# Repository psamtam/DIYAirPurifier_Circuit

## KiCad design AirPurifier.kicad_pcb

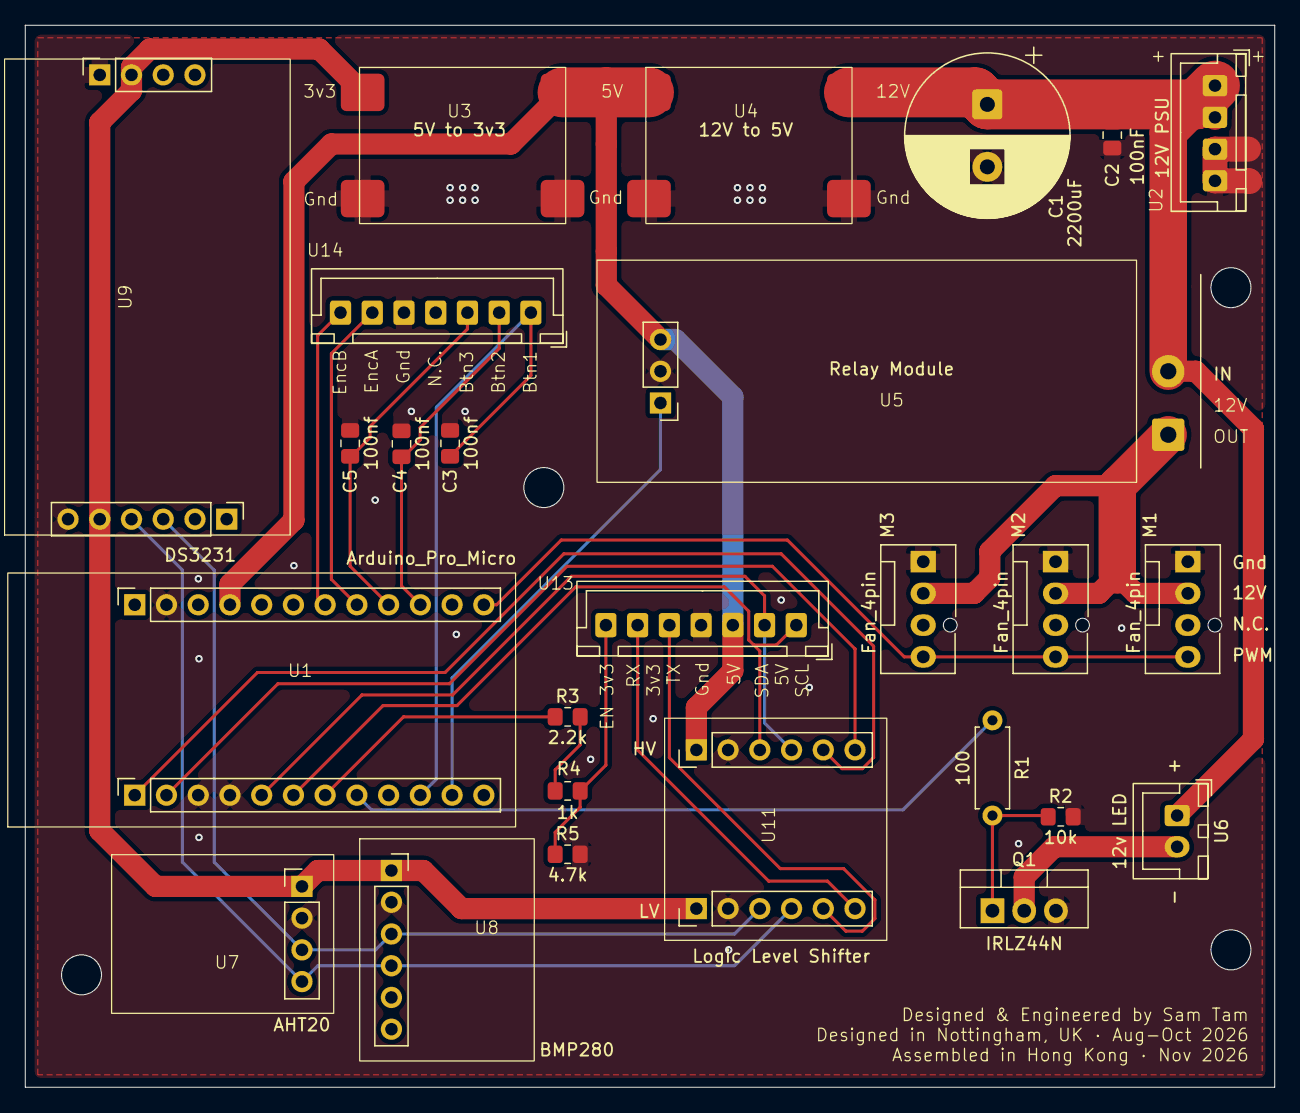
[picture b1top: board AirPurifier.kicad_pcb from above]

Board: 2 copper layers, 100.0 x 85.0 mm, 30 parts (0 on the bottom side), 26 nets.

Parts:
C1: 2200uF; CP_Radial_D13.0mm_P5.00mm
C2: 100nF; C_0805_2012Metric_Pad1.18x1.45mm_HandSolder
C3, C4, C5: 100nf; C_0805_2012Metric_Pad1.18x1.45mm_HandSolder
H1, H2, H3, H4: MountingHole; MountingHole_3.2mm_M3
M1, M2, M3: Fan_4pin; FanPinHeader_1x04_P2.54mm_Vertical
Q1: IRLZ44N; TO-220-3_Vertical
R1: 100; R_Axial_DIN0207_L6.3mm_D2.5mm_P7.62mm_Horizontal
R2: 10k; R_0805_2012Metric_Pad1.20x1.40mm_HandSolder
R3: 2.2k; R_0805_2012Metric_Pad1.20x1.40mm_HandSolder
R4: 1k; R_0805_2012Metric_Pad1.20x1.40mm_HandSolder
R5: 4.7k; R_0805_2012Metric_Pad1.20x1.40mm_HandSolder
U1: Arduino_Pro_Micro; ArduinoProMicro
U2: 12V PSU; XH2.54_4Pin
U3: 5V to 3v3; DCStepDown
U4: 12V to 5V; DCStepDown
U5: Relay Module; RelayModule
U6: 12v LED; JST_XH_B2B-XH-A_1x02_P2.50mm_Vertical
U7: AHT20
U8: BMP280
U9: DS3231
U11: Logic Level Shifter; LogicLevelShifter
U13, U14: XH2.54_7Pin

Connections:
3.3V: U3.1 (3v3), U7.1 (VCC), U8.1 (VCC), U9.5 (VCC), U9.9 (VCC), U11.1 (LV)
5V: U1.21 (VCC), U3.3 (5V), U4.1 (5V), U5.6 (VCC), U11.12 (HV), U13.3 (5V)
12V: C1.1, C2.1, U2.1 (12V), U2.2 (12V), U4.3 (12V), U5.2 (Common), U6.1 (12V)
12V Fan: M1.2 (+), M2.2 (+), M3.2 (+), U5.1 (NO)
Btn2: C4.1, U1.15 (14), U14.2 (Btn2)
Btn3: C5.1, U1.16 (15), U14.3 (Btn3)
External Interrupt Btn1: C3.1, U1.10 (7), U14.1 (Btn1)
Fan PWM: M1.4 (PWM), M2.4 (PWM), M3.4 (PWM), U1.13 (10)
Gnd: C1.2, C2.2, C3.2, C4.2, C5.2, M1.1 (-), M2.1 (-), M3.1 (-), Q1.3 (S), R2.2, R5.2, U1.3 (GND), U1.4 (GND), U1.23 (GND), U2.3 (Gnd), U2.4 (Gnd), U3.2 (Gnd), U3.4 (Gnd), U4.2 (Gnd), U4.4 (Gnd), U5.5 (GND), U7.2 (GND), U8.2 (GND), U9.6 (GND), U9.10 (GND), U11.2 (GND), U11.11 (Gnd), U13.4 (Gnd), U14.5 (Gnd)
LED PWM: R1.1, U1.8 (5)
unnamed: Q1.2 (D), U6.2 (Gnd)
unnamed: Q1.1 (G), R1.2, R2.1
unnamed: R3.2, R4.1
PMS7003 EN 3v3: R4.2, R5.1, U13.7 (PMS7003En)
PMS7003 EN 5v: R3.1, U1.7 (4)
RX 3v3: U11.6 (LV4), U13.6 (RX)
RX 5V: U1.2 (RX1), U11.7 (HV4)
Relay Control: U1.11 (8), U5.4 (IN)
RotaryEncoderA: U1.17 (A0), U14.6 (RotaryEncoderA)
RotaryEncoderB: U1.18 (A1), U14.7 (RotaryEncoderB)
SCL 3v3: U7.3 (SCL), U8.3 (SCL), U9.3 (SCL), U11.3 (LV1)
SCL 5V: U1.6 (3), U11.10 (HV1), U13.1 (SCL)
SDA 3v3: U7.4 (SDA), U8.4 (SDA), U9.4 (SDA), U11.4 (LV2)
SDA 5V: U1.5 (2), U11.9 (HV2), U13.2 (SDA)
TX 3v3: U11.5 (LV3), U13.5 (TX)
TX 5V: U1.1 (TX0), U11.8 (HV3)
